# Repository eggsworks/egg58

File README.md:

# egg58

The egg58 is a staggered-column, split, low-profile keyboard with 58 keys and per-key RGB. The PCB is reversible (i.e. the same part is used for both hands). This repository contains its design files.

## Layout

The egg58 was designed to remain fairly close in layout to an ANSI 60% keyboard, but with a reduced number of keys and
minimal thumb clusters.

This is a suggested layout, but obviously it is customizable.

## Original variant

The original (wired) keyboard design files can be found in directory [egg58v2](egg58v2).

### Materials

- 2x PCB (from this repo)
- 2x switchplate (from this repo)
- 2x Pro Micro or Elite-C
- 2x 4.7K through hole resistors (for I2C option)
- 2x 3.5mm TRRS jack (PJ-320A)
- 58 Choc sockets
- 58 Choc switches (Choc V1 only)
- 58 diodes (1N4148 or similar, throughhole or SOD123)
- 58 SK6812 Mini-E LEDs
- 1x TRRS cable

### Build instructions

On the back of each board:

- Install LEDs such that the notched corner aligns with the indicator on the silkscreen.
  - Be aware that the orientation of the LEDs changes each row.
- Install diodes, such that the cathode (the side with the line) points toward the square holes (upward). 
  - If using through-hole diodes with the FR4 switchplate, ensure that the leads are trimmed very short on the front, otherwise they may scratch through the switchplate solder mask and short out.
- Install sockets.
- If I2C is being used, install the two resistors beneath the location for the TRRS. (They can be placed on the front instead if desired.)
  - Recommended to use either 2x 4.7K on a single hand, or 4x 10K on both hands.
  - The values are fairly flexible, as long as the total resistance on each line is between 2.2K-10K.
- Solder the two jumpers to select serial/I2C and Elite-C/Pro Micro.
  - The EliteC/ProMicro jumper selects the position of the VBUS/RAW pin, to supply 5v to the LEDs and across the TRRS cable. On the Elite-C, the RAW pin is replaced with an extra I/O pin (B0) and an extra VBUS pin is added above it. Select EliteC in this case, or ProMicro for all others.
  - The Serial/I2C jumper selects which data pin is attached to the TRRS jack. The firmware uses I2C by default, but select Serial if you have customized it.
  - Each jumper should have one "outer" pad soldered to the inner pad. See [Issue #4](https://github.com/eggsworks/egg58/issues/4) for further explanation and a diagram.

On the front:

- Install TRRS.
- Install MCU (preferably in a socket).

Mount the switchplate to the PCB with 5x M2 screws. Nylon screws are recommended. A spacer is recommended between the two layers. Finally, install switches in the sockets.

### Firmware

My [fork of QMK](https://github.com/tmick0/qmk_firmware/tree/egg58/keyboards/egg58) contains default configuration and a keymap for the board.

The configuration will need to be changed if using soft serial instead of I2C, or if your microcontrollers do not use the DFU bootloader.

### Changelog

#### Revision 2.1 - 2023-04-01

- Add support for VBUS from Elite-C

#### Revision 2.0 - 2022-03-04

- Original Chocs are used rather than Choc v2
- There is an option to use soft serial instead of I2C for the bridge transport
- The Elite-C microcontroller is now supported in addition to the Pro Micro
- The LEDs are now north-facing (since that is more suitable for the only shine-through caps for Choc currently available)
- The thumb cluster is now designed for 2x 1.5u instead of one 1.5u and one 2u key
- Keys now use Choc spacing instead of MX (be aware of this when purchasing keycaps)

## Wireless variant

A simplified version designed to be used with ZMK is available in the [egg58bt](egg58bt) directory. This version has no RGB and uses BLE for both connectivity to the host and the split transport.

### Materials

- 2x PCB (from this repo)
- 2x switchplate (from this repo)
- 2x nice!nano microcontrollers
- 58 Choc sockets
- 58 Choc switches (Choc V1 only)
- 58 diodes (1N4148 or similar, throughhole or SOD123)

### Build instructions

Construction is the same as the original variant above, just skip the steps related to the split transport and LEDs.

### Firmware

ZMK support is available from my [zmk-config](https://github.com/tmick0/zmk-config) repo.

### Changelog

#### 2023-02-20

- Created wireless variant

## Accessories

A 3D-printable case compatible with both the original and wireless boards can be found in [egg58v2 case](egg58v2%20case). The case uses M2 threaded heat-set inserts to mount the board.

Minimal tenting stands in 15, 10, and 5 degree variants can be printed from the models in [egg58v2 tenting stands](egg58v2%20tenting%20stands). They also use M2 threaded inserts. The tenting stands are mutually exclusive with the full-bottom case.  Rubber bumpons should be applied to the bottom of the stands, and on the "outside" edge of the PCB where the stands do not attach.

A model for a wrist rest is also available in [egg58v2 wrist rest](egg58v2%20wrist%20rest).

## License

This repository is available under the terms of the [GPL, verison 3](LICENSE).

Some portions are derived from:

- [keyswitches.pretty](https://github.com/daprice/keyswitches.pretty) ([CC BY-SA 4.0](https://creativecommons.org/licenses/by-sa/4.0/))
- [Keebio-Parts.pretty](https://github.com/keebio/Keebio-Parts.pretty) ([MIT](https://github.com/keebio/Keebio-Parts.pretty/blob/master/LICENSE))
- [ProMicroKiCad](https://github.com/Biacco42/ProMicroKiCad) ([MIT](https://github.com/Biacco42/ProMicroKiCad/blob/master/LICENSE))
- [SofleKeyboard](https://github.com/josefadamcik/SofleKeyboard) ([MIT](https://github.com/josefadamcik/SofleKeyboard/blob/master/LICENSE))

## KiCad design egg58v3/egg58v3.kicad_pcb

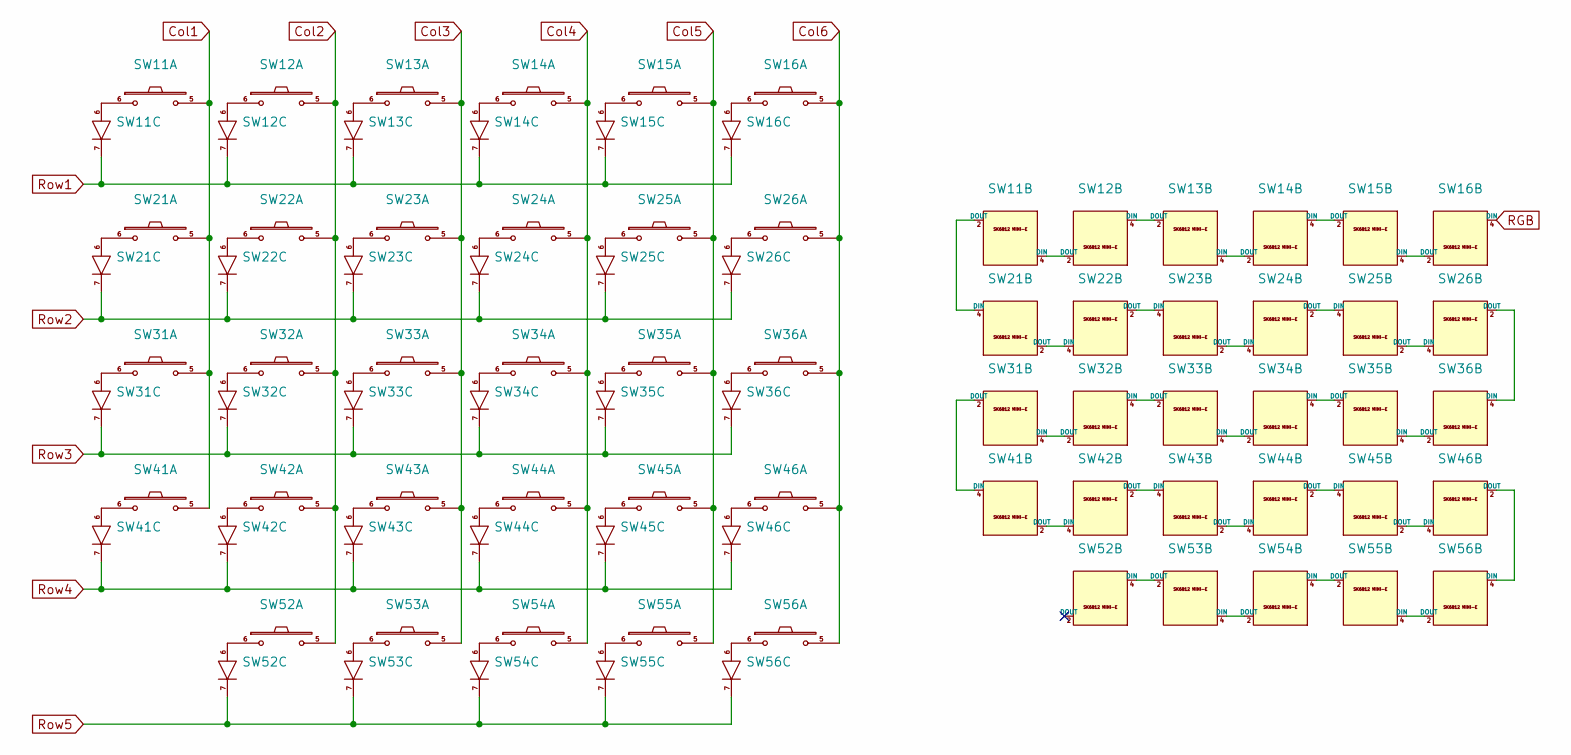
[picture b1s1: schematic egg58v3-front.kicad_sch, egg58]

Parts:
SW11, SW12, SW13, SW14, SW15, SW16, SW21, SW22, SW23, SW24, SW25, SW26, SW31, SW32, SW33, SW34, SW35, SW36, SW41, SW42, SW43, SW44, SW45, SW46, SW52, SW53, SW54: SW_PUSH_LED; Choc_Hotswap_SK6812MiniE
SW55, SW56: SW_PUSH_LED; Choc_Hotswap_SK6812MiniE_Thumb

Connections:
Col1: SW11.5, SW21.5, SW31.5, SW41.5; also elsewhere on the board
Col2: SW12.5, SW22.5, SW32.5, SW42.5, SW52.5; also elsewhere on the board
Col3: SW13.5, SW23.5, SW33.5, SW43.5, SW53.5; also elsewhere on the board
Col4: SW14.5, SW24.5, SW34.5, SW44.5, SW54.5; also elsewhere on the board
Col5: SW15.5, SW25.5, SW35.5, SW45.5, SW55.5; also elsewhere on the board
Col6: SW16.5, SW26.5, SW36.5, SW46.5, SW56.5; also elsewhere on the board
GND: SW11.3 (GND), SW12.3 (GND), SW13.3 (GND), SW14.3 (GND), SW15.3 (GND), SW16.3 (GND), SW21.3 (GND), SW22.3 (GND), SW23.3 (GND), SW24.3 (GND), SW25.3 (GND), SW26.3 (GND), SW31.3 (GND), SW32.3 (GND), SW33.3 (GND), SW34.3 (GND), SW35.3 (GND), SW36.3 (GND), SW41.3 (GND), SW42.3 (GND), SW43.3 (GND), SW44.3 (GND), SW45.3 (GND), SW46.3 (GND), SW52.3 (GND), SW53.3 (GND), SW54.3 (GND), SW55.3 (GND), SW56.3 (GND); also elsewhere on the board
unnamed: SW11.2 (DOUT), SW21.4 (DIN)
unnamed: SW11.4 (DIN), SW12.2 (DOUT)
unnamed: SW12.4 (DIN), SW13.2 (DOUT)
unnamed: SW13.4 (DIN), SW14.2 (DOUT)
unnamed: SW14.4 (DIN), SW15.2 (DOUT)
unnamed: SW15.4 (DIN), SW16.2 (DOUT)
unnamed: SW21.2 (DOUT), SW22.4 (DIN)
unnamed: SW22.2 (DOUT), SW23.4 (DIN)
unnamed: SW23.2 (DOUT), SW24.4 (DIN)
unnamed: SW24.2 (DOUT), SW25.4 (DIN)
unnamed: SW25.2 (DOUT), SW26.4 (DIN)
unnamed: SW26.2 (DOUT), SW36.4 (DIN)
unnamed: SW31.2 (DOUT), SW41.4 (DIN)
unnamed: SW31.4 (DIN), SW32.2 (DOUT)
unnamed: SW32.4 (DIN), SW33.2 (DOUT)
unnamed: SW33.4 (DIN), SW34.2 (DOUT)
unnamed: SW34.4 (DIN), SW35.2 (DOUT)
unnamed: SW35.4 (DIN), SW36.2 (DOUT)
unnamed: SW41.2 (DOUT), SW42.4 (DIN)
unnamed: SW42.2 (DOUT), SW43.4 (DIN)
unnamed: SW43.2 (DOUT), SW44.4 (DIN)
unnamed: SW44.2 (DOUT), SW45.4 (DIN)
unnamed: SW45.2 (DOUT), SW46.4 (DIN)
unnamed: SW46.2 (DOUT), SW56.4 (DIN)
unnamed: SW52.4 (DIN), SW53.2 (DOUT)
unnamed: SW53.4 (DIN), SW54.2 (DOUT)
unnamed: SW54.4 (DIN), SW55.2 (DOUT)
unnamed: SW55.4 (DIN), SW56.2 (DOUT)
RGB: SW16.4 (DIN); also elsewhere on the board
Row1: SW11.7, SW12.7, SW13.7, SW14.7, SW15.7, SW16.7; also elsewhere on the board
Row2: SW21.7, SW22.7, SW23.7, SW24.7, SW25.7, SW26.7; also elsewhere on the board
Row3: SW31.7, SW32.7, SW33.7, SW34.7, SW35.7, SW36.7; also elsewhere on the board
Row4: SW41.7, SW42.7, SW43.7, SW44.7, SW45.7, SW46.7; also elsewhere on the board
Row5: SW52.7, SW53.7, SW54.7, SW55.7, SW56.7; also elsewhere on the board
VCC: SW11.1 (VCC), SW12.1 (VCC), SW13.1 (VCC), SW14.1 (VCC), SW15.1 (VCC), SW16.1 (VCC), SW21.1 (VCC), SW22.1 (VCC), SW23.1 (VCC), SW24.1 (VCC), SW25.1 (VCC), SW26.1 (VCC), SW31.1 (VCC), SW32.1 (VCC), SW33.1 (VCC), SW34.1 (VCC), SW35.1 (VCC), SW36.1 (VCC), SW41.1 (VCC), SW42.1 (VCC), SW43.1 (VCC), SW44.1 (VCC), SW45.1 (VCC), SW46.1 (VCC), SW52.1 (VCC), SW53.1 (VCC), SW54.1 (VCC), SW55.1 (VCC), SW56.1 (VCC); also elsewhere on the board

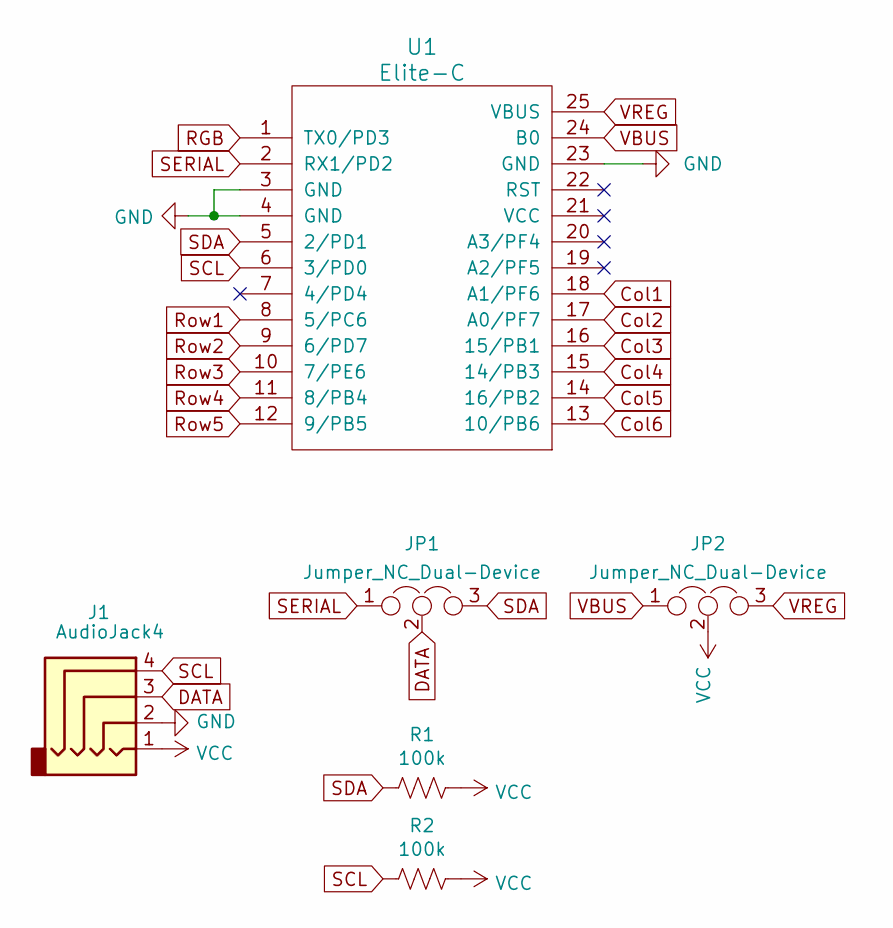
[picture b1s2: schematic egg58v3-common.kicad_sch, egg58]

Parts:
J1: AudioJack4; MJ-4PP-9
JP1, JP2: Jumper_NC_Dual-Device; SolderJumper-3_P1.3mm_Open_Pad1.0x1.5mm_NumberLabels
R1, R2: 100k; R_Axial_DIN0207_L6.3mm_D2.5mm_P10.16mm_Horizontal
U1: Elite-C; ProMicro

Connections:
Col1: U1.18 (A1/PF6); also elsewhere on the board
Col2: U1.17 (A0/PF7); also elsewhere on the board
Col3: U1.16 (15/PB1); also elsewhere on the board
Col4: U1.15 (14/PB3); also elsewhere on the board
Col5: U1.14 (16/PB2); also elsewhere on the board
Col6: U1.13 (10/PB6); also elsewhere on the board
DATA: J1.3, JP1.2
GND: J1.2, U1.3 (GND), U1.4 (GND), U1.23 (GND); also elsewhere on the board
RGB: U1.1 (TX0/PD3); also elsewhere on the board
Row1: U1.8 (5/PC6); also elsewhere on the board
Row2: U1.9 (6/PD7); also elsewhere on the board
Row3: U1.10 (7/PE6); also elsewhere on the board
Row4: U1.11 (8/PB4); also elsewhere on the board
Row5: U1.12 (9/PB5); also elsewhere on the board
SCL: J1.4, R2.2, U1.6 (3/PD0)
SDA: JP1.3, R1.2, U1.5 (2/PD1)
SERIAL: JP1.1, U1.2 (RX1/PD2)
VBUS: JP2.1, U1.24 (B0)
VCC: J1.1, JP2.2, R1.1, R2.1; also elsewhere on the board
VREG: JP2.3, U1.25 (VBUS)

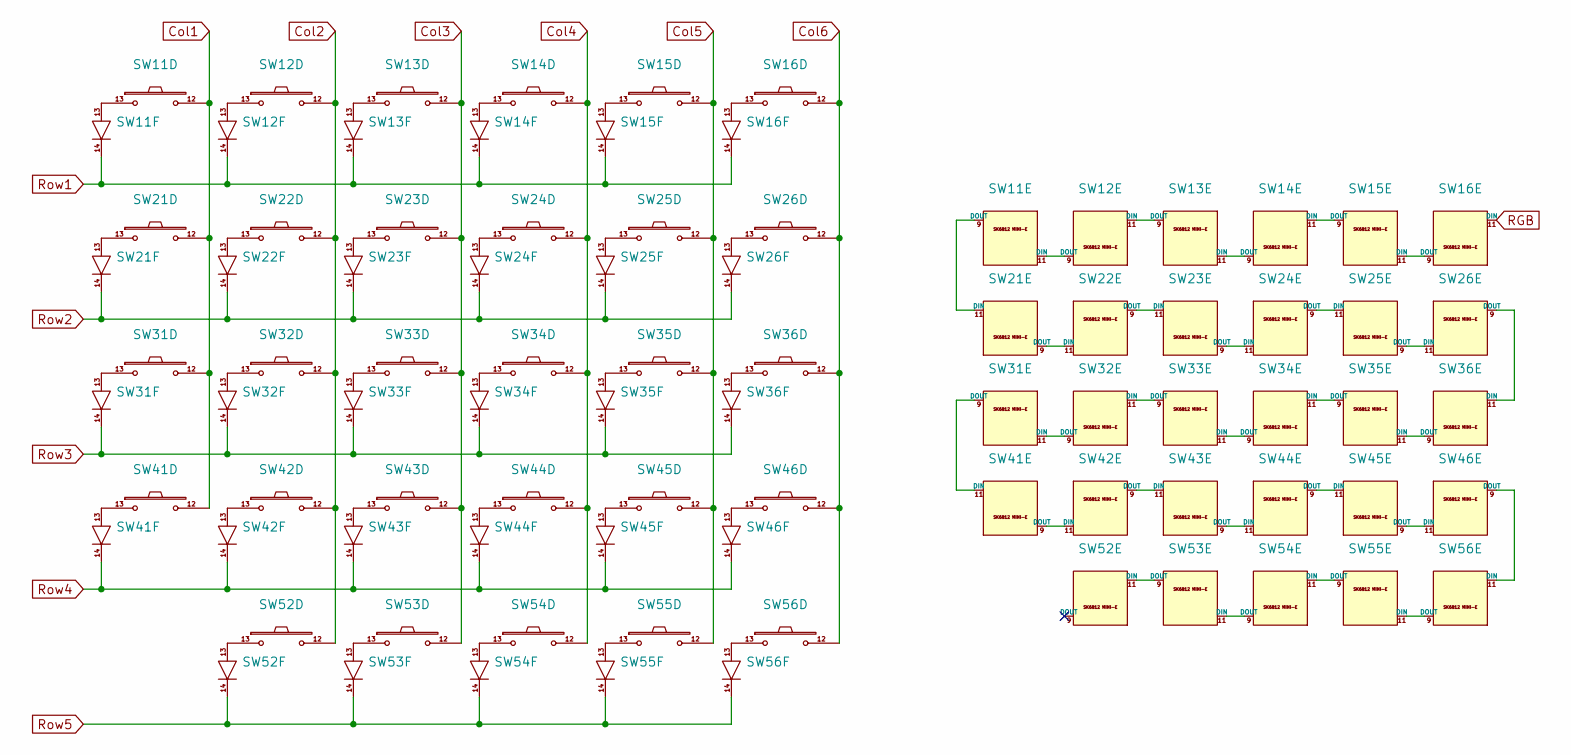
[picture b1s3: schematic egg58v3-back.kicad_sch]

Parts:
SW11, SW12, SW13, SW14, SW15, SW16, SW21, SW22, SW23, SW24, SW25, SW26, SW31, SW32, SW33, SW34, SW35, SW36, SW41, SW42, SW43, SW44, SW45, SW46, SW52, SW53, SW54: SW_PUSH_LED; Choc_Hotswap_SK6812MiniE
SW55, SW56: SW_PUSH_LED; Choc_Hotswap_SK6812MiniE_Thumb

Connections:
Col1: SW11.12, SW21.12, SW31.12, SW41.12; also elsewhere on the board
Col2: SW12.12, SW22.12, SW32.12, SW42.12, SW52.12; also elsewhere on the board
Col3: SW13.12, SW23.12, SW33.12, SW43.12, SW53.12; also elsewhere on the board
Col4: SW14.12, SW24.12, SW34.12, SW44.12, SW54.12; also elsewhere on the board
Col5: SW15.12, SW25.12, SW35.12, SW45.12, SW55.12; also elsewhere on the board
Col6: SW16.12, SW26.12, SW36.12, SW46.12, SW56.12; also elsewhere on the board
GND: SW11.10 (GND), SW12.10 (GND), SW13.10 (GND), SW14.10 (GND), SW15.10 (GND), SW16.10 (GND), SW21.10 (GND), SW22.10 (GND), SW23.10 (GND), SW24.10 (GND), SW25.10 (GND), SW26.10 (GND), SW31.10 (GND), SW32.10 (GND), SW33.10 (GND), SW34.10 (GND), SW35.10 (GND), SW36.10 (GND), SW41.10 (GND), SW42.10 (GND), SW43.10 (GND), SW44.10 (GND), SW45.10 (GND), SW46.10 (GND), SW52.10 (GND), SW53.10 (GND), SW54.10 (GND), SW55.10 (GND), SW56.10 (GND); also elsewhere on the board
unnamed: SW11.9 (DOUT), SW21.11 (DIN)
unnamed: SW11.11 (DIN), SW12.9 (DOUT)
unnamed: SW12.11 (DIN), SW13.9 (DOUT)
unnamed: SW13.11 (DIN), SW14.9 (DOUT)
unnamed: SW14.11 (DIN), SW15.9 (DOUT)
unnamed: SW15.11 (DIN), SW16.9 (DOUT)
unnamed: SW21.9 (DOUT), SW22.11 (DIN)
unnamed: SW22.9 (DOUT), SW23.11 (DIN)
unnamed: SW23.9 (DOUT), SW24.11 (DIN)
unnamed: SW24.9 (DOUT), SW25.11 (DIN)
unnamed: SW25.9 (DOUT), SW26.11 (DIN)
unnamed: SW26.9 (DOUT), SW36.11 (DIN)
unnamed: SW31.9 (DOUT), SW41.11 (DIN)
unnamed: SW31.11 (DIN), SW32.9 (DOUT)
unnamed: SW32.11 (DIN), SW33.9 (DOUT)
unnamed: SW33.11 (DIN), SW34.9 (DOUT)
unnamed: SW34.11 (DIN), SW35.9 (DOUT)
unnamed: SW35.11 (DIN), SW36.9 (DOUT)
unnamed: SW41.9 (DOUT), SW42.11 (DIN)
unnamed: SW42.9 (DOUT), SW43.11 (DIN)
unnamed: SW43.9 (DOUT), SW44.11 (DIN)
unnamed: SW44.9 (DOUT), SW45.11 (DIN)
unnamed: SW45.9 (DOUT), SW46.11 (DIN)
unnamed: SW46.9 (DOUT), SW56.11 (DIN)
unnamed: SW52.11 (DIN), SW53.9 (DOUT)
unnamed: SW53.11 (DIN), SW54.9 (DOUT)
unnamed: SW54.11 (DIN), SW55.9 (DOUT)
unnamed: SW55.11 (DIN), SW56.9 (DOUT)
RGB: SW16.11 (DIN); also elsewhere on the board
Row1: SW11.14, SW12.14, SW13.14, SW14.14, SW15.14, SW16.14; also elsewhere on the board
Row2: SW21.14, SW22.14, SW23.14, SW24.14, SW25.14, SW26.14; also elsewhere on the board
Row3: SW31.14, SW32.14, SW33.14, SW34.14, SW35.14, SW36.14; also elsewhere on the board
Row4: SW41.14, SW42.14, SW43.14, SW44.14, SW45.14, SW46.14; also elsewhere on the board
Row5: SW52.14, SW53.14, SW54.14, SW55.14, SW56.14; also elsewhere on the board
VCC: SW11.8 (VCC), SW12.8 (VCC), SW13.8 (VCC), SW14.8 (VCC), SW15.8 (VCC), SW16.8 (VCC), SW21.8 (VCC), SW22.8 (VCC), SW23.8 (VCC), SW24.8 (VCC), SW25.8 (VCC), SW26.8 (VCC), SW31.8 (VCC), SW32.8 (VCC), SW33.8 (VCC), SW34.8 (VCC), SW35.8 (VCC), SW36.8 (VCC), SW41.8 (VCC), SW42.8 (VCC), SW43.8 (VCC), SW44.8 (VCC), SW45.8 (VCC), SW46.8 (VCC), SW52.8 (VCC), SW53.8 (VCC), SW54.8 (VCC), SW55.8 (VCC), SW56.8 (VCC); also elsewhere on the board

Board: 2 copper layers, 35 parts (19 on the bottom side), 76 nets, no tracks yet.

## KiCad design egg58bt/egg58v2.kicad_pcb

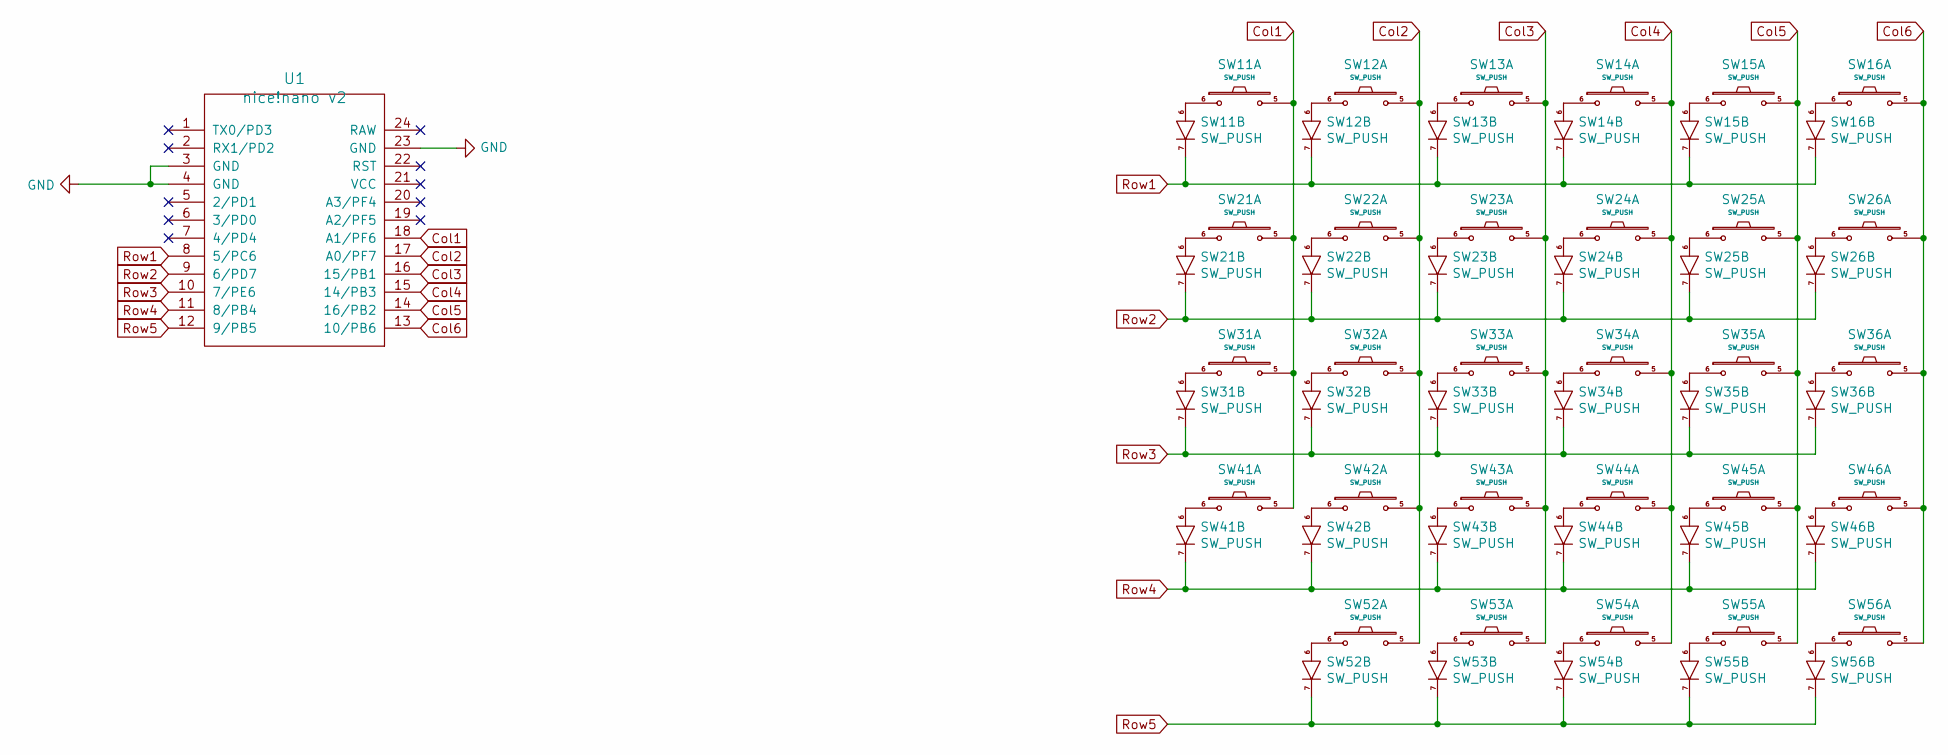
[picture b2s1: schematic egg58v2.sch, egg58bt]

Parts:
SW11, SW12, SW13, SW14, SW15, SW16, SW21, SW22, SW23, SW24, SW25, SW26, SW31, SW32, SW33, SW34, SW35, SW36, SW41, SW42, SW43, SW44, SW45, SW46, SW52, SW53, SW54, SW55, SW56: SW_PUSH; Choc_Hotswap
U1: nice!nano v2; ProMicro

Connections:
Col1: SW11.5, SW21.5, SW31.5, SW41.5, U1.18 (A1/PF6)
Col2: SW12.5, SW22.5, SW32.5, SW42.5, SW52.5, U1.17 (A0/PF7)
Col3: SW13.5, SW23.5, SW33.5, SW43.5, SW53.5, U1.16 (15/PB1)
Col4: SW14.5, SW24.5, SW34.5, SW44.5, SW54.5, U1.15 (14/PB3)
Col5: SW15.5, SW25.5, SW35.5, SW45.5, SW55.5, U1.14 (16/PB2)
Col6: SW16.5, SW26.5, SW36.5, SW46.5, SW56.5, U1.13 (10/PB6)
GND: U1.3 (GND), U1.4 (GND), U1.23 (GND)
Row1: SW11.7, SW12.7, SW13.7, SW14.7, SW15.7, SW16.7, U1.8 (5/PC6)
Row2: SW21.7, SW22.7, SW23.7, SW24.7, SW25.7, SW26.7, U1.9 (6/PD7)
Row3: SW31.7, SW32.7, SW33.7, SW34.7, SW35.7, SW36.7, U1.10 (7/PE6)
Row4: SW41.7, SW42.7, SW43.7, SW44.7, SW45.7, SW46.7, U1.11 (8/PB4)
Row5: SW52.7, SW53.7, SW54.7, SW55.7, SW56.7, U1.12 (9/PB5)

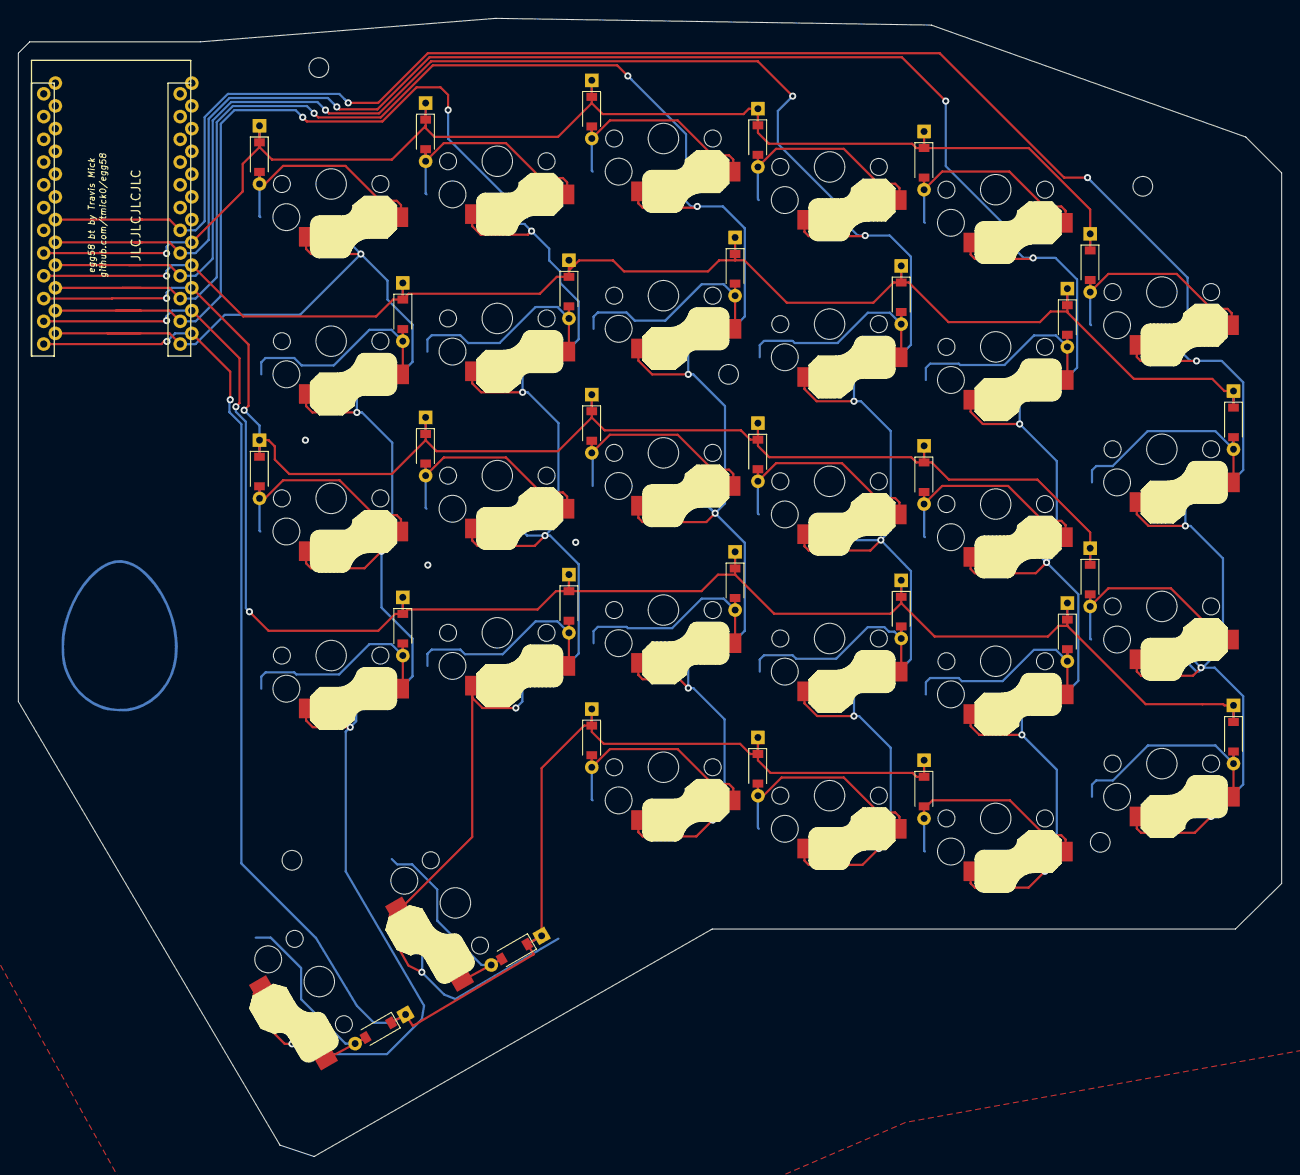
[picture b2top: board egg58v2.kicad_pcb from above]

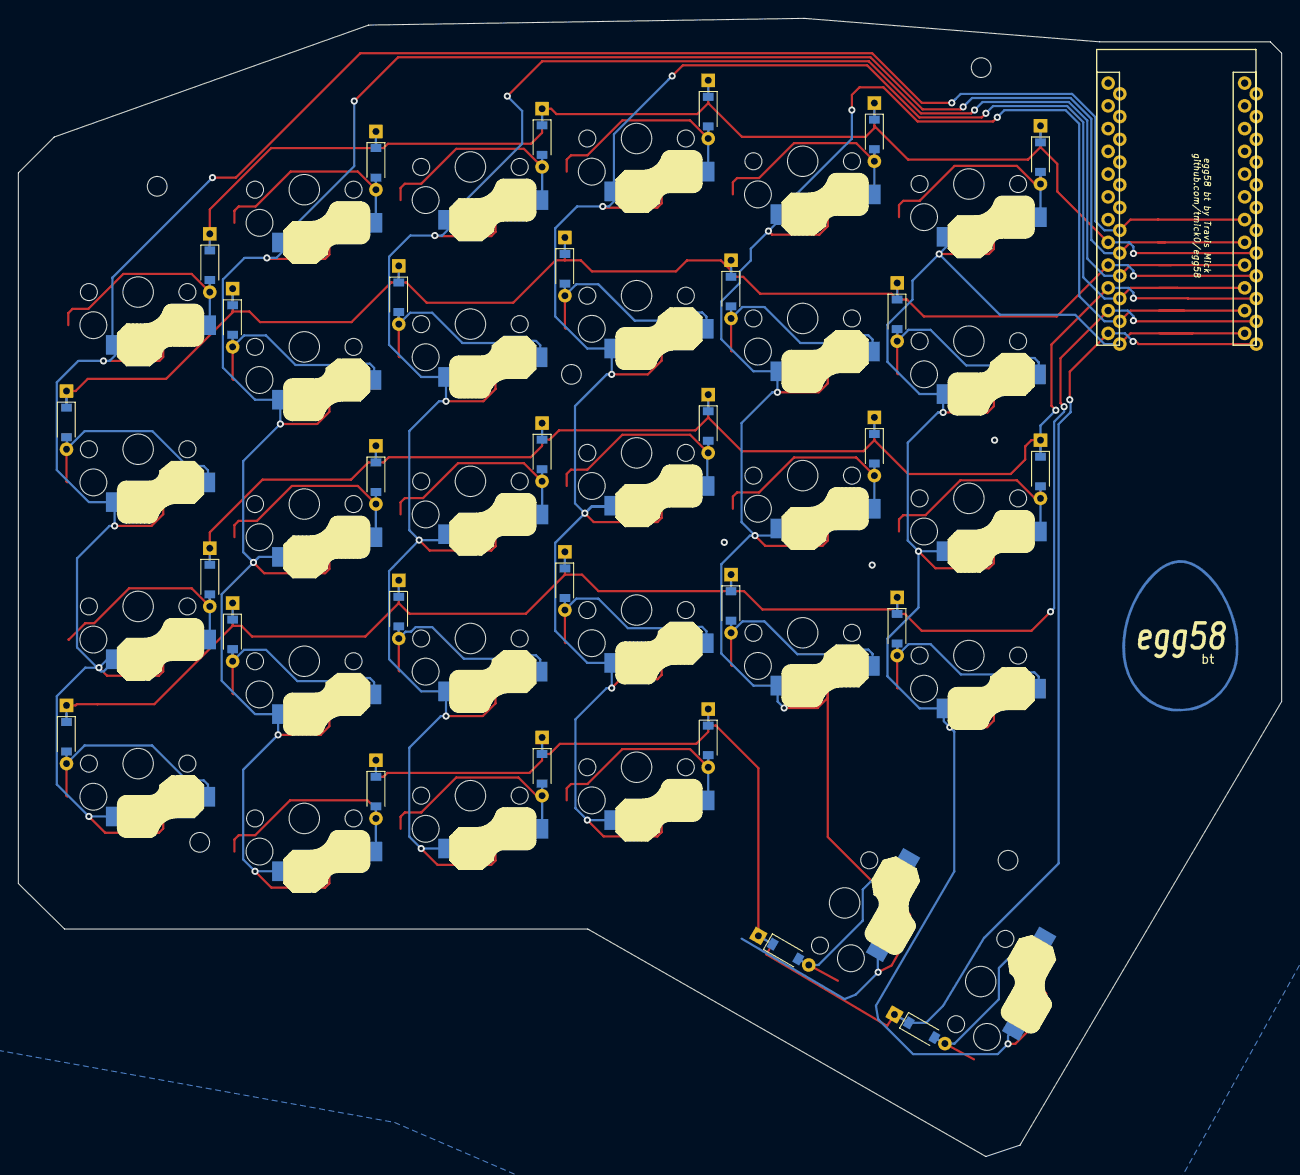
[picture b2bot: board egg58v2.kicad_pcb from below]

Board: 2 copper layers, 141.1 x 127.1 mm, 30 parts (16 on the bottom side), 12 nets.

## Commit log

2022-01-23 Add license and readme
2022-01-26 update to choc switch spacing, add logo
2022-01-26 footprint updates
2022-01-26 add images
2022-01-28 make LEDs north facing
2022-01-28 add option for i2c back
2022-01-28 starting routing
2022-01-30 starting routing for matrix
2022-01-31 routing fixes
2022-01-31 columns
2022-02-19 underp footprints and route everything i guess
2022-02-19 fix (most) vias through silks
2022-03-04 Mounting holes
2022-03-04 First draft of switchplate
2022-03-04 Final touches on switchplate
2022-04-12 Update readme with qmk link and photo
2022-06-29 Add support for VBUS from EliteC
2023-01-10 Add wrist rest stl
2023-03-10 Add wireless egg58
2023-03-21 Add wireless egg58 (#2)
2023-04-01 Update wrist rest STL, add case STL, update readme
2023-04-07 Initial setup for egg58v3
    The new version updates footprints to exact 18x17mm key spacing,
    removing the extra .5mm gap from the egg58v2. Support for THT
    diodes has been removed. Footprints and symbols have also been
    updated to better separate the two sides of the board. This should
    simplify routing.
2023-04-07 Initial layout for v3
2023-05-24 Clarification on jumper configuration
2023-06-01 Update case, add tenting stands
2023-06-01 Add info on tenting stands to readme
2023-06-01 Fix typos
2023-12-04 Add tented wrist rest
2023-12-04 Move flat wrist rest to subdir
2023-12-04 Remove duplicate files
